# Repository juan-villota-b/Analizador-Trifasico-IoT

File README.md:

# Analizador Trifásico IoT

> Instrumento electrónico industrial de **medición eléctrica trifásica** con conectividad **IoT**.
> Orientado a instalaciones industriales y motores: registro de consumo, variables eléctricas a múltiples escalas de tiempo, comunicación **Modbus RTU / RS-485** y enlace inalámbrico **Wi-Fi HaLow**.

**Estado del diseño:** diseño final **Rev. 1.0 (05/11/2026)** — esquemáticos capturados, layout en curso.

---

## 🧭 Diagrama de bloques final

Este es el diseño vigente. Toda decisión de hardware debe ser consistente con este diagrama:

📎 [`Diagrama_de_bloques_final.pdf`](documentation/Diagrama_de_bloques_final.pdf) · [`PNG`](documentation/Diagrama_de_bloques_final.png) · [`SVG`](documentation/Diagrama_de_bloques_final.svg)

> El diagrama V2 (`documentation/Diagrama de bloquesv2.pdf`, 07/10/2026) se conserva como historial. El diseño vigente es el de esta página.

---

## 🔧 Arquitectura por bloque

### 1. Entrada de potencia trifásica

| Elemento | Componente | Notas |
|---|---|---|
| Entrada | **Red trifásica L1 / L2 / L3 / N** | **3P4W, 120/208 V** |
| Conector | **U301** — bornera 4 vías, 5 mm | N · L3 · L2 · L1, 10 A |
| Protección | **F300–F302** + **RV300–RV302** | Fusibles 2410 *time-lag* + MOV-14D471K por fase |
| Entrada de CT | **4× HX PJ-320A-3P DIP** (U300, U302, U303, U304) | Tres fases + neutro |

**Conexionado de los jacks de CT:** pin 2 = *tip* (señal), pin 3 = *sleeve* (retorno), pin 4 = *switch*. El pin 4 se une al pin 3 para cortocircuitar el CT cuando no hay plug; al insertar el plug, el switch abre y el CT queda con su burden. Cada pierna lleva **5.1 Ω** a AGND, **1 kΩ** en serie y **33 nF** de filtro.

> Hoja: `THREE PHASES.SchDoc`

### 2. Acondicionamiento analógico

| Elemento | Descripción |
|---|---|
| Canales de tensión | 3 canales diferenciales: **6×165 kΩ + 1 kΩ** por fase, **33 nF** a AGND |
| Canales de corriente | 4 canales diferenciales: burden **5.1 Ω** por pierna, **1 kΩ** serie, **33 nF** |
| Rango del AFE | **830 mVp** por canal diferencial |
| Filtrado | RC de entrada y guard ring en el layout |

El divisor de tensión usa resistencias de **165 kΩ ±0.1 %** y **1 kΩ** en la base. El burden de corriente es de **10.2 Ω diferencial** (5.1 Ω por pierna), compatible con un CT de **100 A / 40 mA** (577 mVp).

> Hoja: `THREE PHASES.SchDoc` (derivaciones) + `MEASURES.SchDoc`

### 3. AFE metrológico

| Elemento | Componente |
|---|---|
| Medidor | **RENERGY RN8302B** (LQFP-44) |
| Canales | 3 de tensión + 4 de corriente, diferenciales |
| Reloj | Cristal **8.192 MHz** (`049ss2-8.192f12dzlal`) |
| Desacople | 10 µF + 100 nF por riel, 1 µF local, ferrita FB100 |
| Alimentación | **AVCC/DVCC 3.3 V** desde el dominio de medida |

Calcula V, I, P, Q, S, PF y THD internamente. El ESP32-S3 lee los registros por SPI a través del ISO7741.

> Hoja: `MEASURES.SchDoc`

### 4. Aislamiento galvánico

| Elemento | Componente |
|---|---|
| Aislador digital | **TI ISO7741DWR** (4 canales, 5000 Vrms) |
| Alimentación aislada del AFE | **B0503S-1WR3** (5 V → 3.3 V, 1 W, 1500 VDC) |
| Señales aisladas | **SPI de 4 hilos** entre RN8302B y ESP32-S3 |

**Mapa del SPI aislado:**

| Señal | ESP32-S3 | ISO7741 | RN8302B |
|---|---|---|---|
| MOSI | `IO14` (pin 22) | INA 3 → OUTA 14 | SDI 35 |
| CS | `IO21` (pin 23) | INB 4 → OUTB 13 | SCSN 34 |
| CLK | `IO47` (pin 24) | INC 5 → OUTC 12 | SCLK 33 |
| MISO | `IO48` (pin 25) | OUTD 6 ← IND 11 | SDO 32 |

El dominio de medida queda referenciado a **AGND = N**; el dominio digital a **DGND**; el RS-485 a **RGND**. El ISO7741 y el B0503S son los puentes de la barrera.

> Hoja: `MEASURES.SchDoc`

### 5. Procesamiento

| Elemento | Componente |
|---|---|
| MCU | **ESP32-S3-WROOM-1-N4** |
| Programación | **USB-C** (`CON_USB_TYPEC_16P`) — USB nativo / JTAG integrado |
| Monitorización | Puerto serie por USB |
| Arranque | Botones **EN** y **BOOT**, RC de 10 kΩ + 1.1 µF |

> Hoja: `MCU.SchDoc`

### 6. Alimentación

| Riel | Componente | Capacidad | Destino |
|---|---|---|---|
| AC/DC principal | **Hi-Link HLK-10M05** | 5 V @ 2 A (10 W) | Riel de 5 V y respaldo |
| OR-ing de 5 V | **D200** (MS2A40LWS) | — | `Vin_buck_5V` |
| Carga de respaldo | **TPS2553DRVR** + **2×30 F** | 15 F equivalentes | *Last Gasp* |
| OR-ing de respaldo | **D201** (MS2A40LWS) | — | `Vin_buck_5V` |
| Riel digital | **AP63203WU-7** | **3.3 V @ 2 A** | ESP32-S3, SD, RS-485, HaLow |
| Riel de medida | **B0503S-1WR3** | **3.3 V @ 1 W aislado** | RN8302B, ISO7741 lado 2 |

#### Presupuesto de corriente del riel 3.3 V

| Carga | Consumo |
|---|---:|
| ESP32-S3-WROOM | 500 mA |
| Quectel FGH100M (Wi-Fi HaLow) | 350 mA |
| microSD | 200 mA |
| VISOM RSM3485PCT (RS-485) | 90 mA |
| RN8302B + ISO7741 | 20 mA |
| **Total** | **1 160 mA** |
| Capacidad del buck AP63203 | 2 000 mA |
| **Margen** | **840 mA (42 %)** |

#### Respaldo *Last Gasp*

- Banco: **2×30 F = 15 F** equivalentes, cargado a ≈4.6 V.
- Energía útil hasta ≈4.2 V: **≈26 J**.
- Autonomía: **≈8 s a 3.2 W**, suficiente para cerrar el registro y notificar.
- La rama de carga se limita con el **TPS2553**; el detalle de coordinación está en `REPORT.md`.

> Hoja: `POWER.SchDoc`

### 7. Periféricos

| Periférico | Componente | Interfaz con el ESP32-S3 | Consumo |
|---|---|---|---|
| **RS-485** | **VISOM RSM3485PCT** | UART `IO17/IO18` + `CON` `IO16` | 90 mA |
| **Wi-Fi HaLow** | **Quectel FGH100M** (módulo externo) | SPI compartido + control | 350 mA (3.3 V) |
| **Almacenamiento** | **microSD** (`tf-card-9p`) | SPI `IO11/IO12/IO13`, CS `IO38` | 200 mA |
| **USB** | **USB-C** | D−/D+ `IO19/IO20` | — |

**Conexión del módulo HaLow (headers 500/501):**

| Header | Pin | Señal | GPIO |
|---|---:|---|---|
| 500 | 1 | `RST_H` | `IO5` |
| 500 | 2 | `WK_IN_H` | `IO6` |
| 500 | 3 | `SPI_IRQ_H` | `IO7` |
| 500 | 4 | `SPI_CS_H` | `IO10` |
| 501 | 2 | `SPI_CLK_H` | `IO12` |
| 501 | 3 | `SPI_MISO_H` | `IO13` |
| 501 | 4 | `SPI_MOSI_H` | `IO11` |
| 501 | 5 | 3.3 V | — |
| 501 | 6 | DGND | — |
| 501 | 7 | 5 V | — |

La microSD y el FGH100M comparten el bus SPI (`IO11/IO12/IO13`) con CS independientes (`IO38` y `IO10`). El RN8302B tiene un bus SPI dedicado y aislado, por lo que no comparte MISO con la SD ni con el HaLow.

> Hojas: `MCU.SchDoc` + `INTERFACES.SchDoc`

---

## 📌 Mapa de interfaces del ESP32-S3-WROOM

| Interfaz | Pines | Hacia |
|---|---|---|
| SPI aislado del AFE | `IO14` MOSI, `IO21` CS, `IO47` CLK, `IO48` MISO | RN8302B vía ISO7741 |
| SPI de microSD / HaLow | `IO11` MOSI, `IO12` CLK, `IO13` MISO | microSD (`CS IO38`) y FGH100M (`CS IO10`) |
| UART RS-485 | `IO17` TX, `IO18` RX, `IO16` CON | RSM3485PCT |
| Control HaLow | `IO5` RST, `IO6` WAKE, `IO7` IRQ, `IO10` CS | Headers 500/501 |
| USB | `IO19` D−, `IO20` D+ | USB-C |
| Arranque | `IO0` BOOT, pin 3 EN | Botones y RC |
| Tarjeta SD | `IO9` CD | Conector microSD |

---

## ⚡ Arquitectura de energía

```
Red 3P4W 120/208 V
        │
        └──► U301 ─► F300 ─► HLK-10M05 (5 V @ 2 A)
                                   │
                                   └──► D200 ─► 5 V (Vin_buck_5V)
                                              ├──► AP63203 ─► 3.3 V digital
                                              │        └──► ESP32-S3 · microSD · RS-485 · HaLow
                                              ├──► TPS2553 ─► 2×30 F (15 F) ─► D201 ─► 5 V respaldo
                                              └──► B0503S-1WR3 ─► 3.3 V aislado ─► RN8302B + ISO7741
```

El **HLK-10M05** es la única fuente AC/DC y alimenta el riel de 5 V. El **AP63203** genera el riel digital de 3.3 V; el **B0503S-1WR3** genera el riel aislado de 3.3 V para el AFE. El **TPS2553** carga el banco de supercapacitores y el **D201** lo conecta al riel de 5 V durante el respaldo.

---

## 🗂️ Estructura del repositorio

```
Analizador trifasico IoT/
├── README.md
├── REPORT.md                       ← auditoría pin a pin y verificaciones de cierre
├── CONTRIBUTING.md                 ← guía de trabajo en equipo
├── INSTRUCCIONES.md                ← guía de layout y fabricación
├── AGENTS.md                       ← reglas para agentes de IA
├── .gitignore / .gitattributes
│
├── hardware/
│   ├── altium/                     ← Proyecto Altium Designer (fuente de verdad)
│   │   ├── Analizador_trifasico_IoT_pcb.PrjPcb
│   │   ├── Analizador_trifasico_IoT_pcb.PrjPcbStructure
│   │   ├── MAIN.SchDoc             ← hoja raíz
│   │   ├── THREE PHASES.SchDoc     ← entrada trifásica, CT y divisores
│   │   ├── POWER.SchDoc            ← alimentación, respaldo y rieles
│   │   ├── MEASURES.SchDoc         ← RN8302B + ISO7741 + cristal
│   │   ├── MCU.SchDoc              ← ESP32-S3, USB-C, EN/BOOT
│   │   ├── INTERFACES.SchDoc       ← RS-485, microSD, headers HaLow
│   │   └── Analizador_PCB.PcbDoc   ← layout
│   │
│   └── libraries/                  ← Biblioteca única del proyecto
│       ├── Library_Analizador.LibPkg
│       ├── Schlib1.SchLib
│       ├── PcbLib1.PcbLib
│       └── Library_Analizador.IntLib
│
├── documentation/
│   ├── Diagrama_de_bloques_final.pdf / .png / .svg
│   ├── Diagrama de bloquesv2.pdf   ← historial
│   ├── application-note/           ← nota de aplicación (LaTeX + PDF)
│   ├── revision_v3/                ← diagramas de la revisión anterior
│   ├── wifi-module-halow-xiao/     ← documentación del módulo HaLow
│   └── RD_EM_01_Industrial_Energy_Monitor.pdf
│
├── references/
│   ├── datasheets/
│   ├── application-notes/
│   └── reference-designs/
│
└── software/                       ← herramientas de visualización y pruebas
```

> `INSTRUCCIONES.md` conserva la guía de layout de la revisión anterior. Para la conectividad vigente usa `REPORT.md` y el netlist del 05/11/2026.

---

## 🔌 Hojas del esquemático

| # | Archivo | Contenido | Componentes clave |
|---|---|---|---|
| 1 | `MAIN.SchDoc` | Hoja raíz: solo *sheet symbols* | — |
| 2 | `THREE PHASES.SchDoc` | Entrada trifásica, CT y divisores | U301, F300–F302, RV300–RV302, U300/U302/U303/U304, R303–R339, C300–C313 |
| 3 | `POWER.SchDoc` | Alimentación, respaldo y rieles | HLK-10M05, D200/D201/D202, TPS2553, 2×30 F, AP63203, B0503S-1WR3 |
| 4 | `MEASURES.SchDoc` | AFE metrológico y aislamiento | RN8302B, ISO7741, cristal 8.192 MHz, desacople |
| 5 | `MCU.SchDoc` | Procesamiento y USB | ESP32-S3-WROOM-1-N4, USB-C, EN/BOOT |
| 6 | `INTERFACES.SchDoc` | Comunicaciones y almacenamiento | RSM3485PCT, tf-card-9p, headers 500/501, SM712 |

---

## 📚 Referencias técnicas

### `references/datasheets/`

| Archivo | Componente |
|---|---|
| `RN8302B_Datasheet_v3.pdf` | RENERGY RN8302B — AFE metrológico |
| `RN8302B_User_Manual_v1.1.pdf` | RENERGY RN8302B — manual de usuario |
| `ESP32-S3_Datasheet_en.pdf` | Espressif ESP32-S3 — SoC |
| `ESP32-S3_Technical_Reference_Manual_en.pdf` | Espressif ESP32-S3 — manual técnico |
| `ESP32-S3-WROOM_Module.pdf` | Espressif ESP32-S3-WROOM-1-N4 — módulo |
| `ISO7741DWR_Datasheet.pdf` | TI ISO7741 — aislador digital cuádruple |
| `EVISUN B0503S-1WR3.pdf` | B0503S-1WR3 — DC-DC aislado 5 V → 3.3 V |
| `TI TPS2553DRVR.pdf` | TPS2553 — interruptor/cargador limitado |
| `AP63203WU-7_Datasheet.pdf` | AP63203 — buck 3.3 V |
| `HLK-10M05_Datasheet.pdf` | Hi-Link HLK-10M05 — AC/DC 5 V 2 A |
| `RSM3485PCT_Datasheet.pdf` | VISOM RSM3485PCT — RS-485 aislado |
| `TF-CARD-9P_Datasheet.pdf` | Conector microSD |
| `HX-PJ-320A-3P_Datasheet.pdf` | Jack PJ-320A-3P |
| `Supercapacitor_Datasheet.pdf` | Supercapacitor HP-2R7-J306VYJ23 |
| `JFC2410-0200TS_Datasheet.pdf` | Fusible 2410 |
| `MOV-14D471K_Datasheet.pdf` | Varistor MOV-14D471K |

### `references/application-notes/`

| Archivo | Contenido |
|---|---|
| `TI_DUF27A_Application_Note.pdf` | TI DUF27A — nota de aplicación |
| `TI_DUF27A_Layout.pdf` | TI DUF27A — guías de layout |
| `wifi-halow-module-for-xiao.md` | Notas del módulo Wi-Fi HaLow |

### `references/reference-designs/`

| Carpeta | Contenido |
|---|---|
| `EVAL-ADE9430/` | Analog Devices EVAL-ADE9430 — referencia de AFE trifásico |
| `WI-FI_HALOW_FGH100M_EXT01_V30/` | Módulo HaLow: PCB, esquemático PDF e importación a Altium |
| `HX PJ-320A-3P DIP/` | Conector HX PJ-320A-3P DIP — footprint y símbolo |
| `TI_DCG_v3/` | Gerber / ODB++ de referencia |

---

## 🚀 Cómo empezar a colaborar

> 📘 **Guía completa paso a paso: [`CONTRIBUTING.md`](CONTRIBUTING.md)**

### Ciclo de trabajo

```bash
git checkout main
git pull
git checkout -b feature/mi-tarea
# ... trabajar en Altium, guardar y CERRAR Altium ...
git status
git add .
git commit -m "MEASURES: ajusta rango de ADC de corriente"
git push -u origin feature/mi-tarea
# → Pull Request en GitHub → revisión → merge → borrar rama
```

Si `main` avanzó antes del merge:

```bash
git checkout main && git pull
git checkout feature/mi-tarea
git merge main
git push
```

> ⚠️ **Cierra Altium antes de `git pull`, `git checkout` o `git merge`.** Si está abierto, sobrescribe el archivo al guardar y se pierde el trabajo del compañero.

### Reglas de colaboración

Los archivos `.SchDoc`, `.PcbDoc`, `.SchLib` y `.PcbLib` son **binarios** (contenedores OLE2):

| Git **SÍ** puede | Git **NO** puede |
|---|---|
| Guardar el historial completo | Mostrar diffs de contenido (`Binary files differ`) |
| Revertir a cualquier versión | Fusionar cambios automáticamente |
| Crear ramas independientes | Resolver conflictos de merge |

1. **Una persona por archivo a la vez.** En especial `Analizador_PCB.PcbDoc` — es monolítico.
2. **Una rama por tarea**, nunca trabajes directamente en `main`.
3. **Nunca dos personas en la misma rama ni el mismo archivo en dos ramas.**
4. **Cierra Altium antes de cualquier operación de Git.**
5. **Si hay conflicto de merge en un binario**, no lo edites a mano: coordina con el compañero y rehaz el cambio en Altium sobre la versión que quede en `main`.

---

## 📄 Convención de commits

```
<hoja o bloque>: <descripción corta en imperativo>

THREE PHASES: ajusta entrada de CT
POWER: actualiza respaldo de supercaps
MEASURES: ajusta desacople del RN8302B
MCU: conecta SPI de la microSD
INTERFACES: ordena headers del HaLow
PCB: enruta zona de potencia
LIB: actualiza símbolo del RSM3485PCT
DOC: actualiza diagrama de bloques final
```

---

## 📊 Estado del proyecto

**Diseño final**
- [x] Arquitectura de hardware Rev. 1.0 (05/11/2026)
- [x] Diagrama de bloques final (PDF/PNG/SVG)
- [x] Esquemáticos de las 6 hojas capturados
- [x] Netlist y BOM del proyecto
- [x] Biblioteca única del proyecto
- [x] Nota de aplicación y documentación de referencia

**Verificaciones de cierre antes de fabricar**

| Tema | Verificación |
|---|---|
| CT | Seleccionar el modelo (100 A / 40 mA recomendado), confirmar burden 5.1 Ω y 830 mVp. |
| Entrada | Confirmar 120/208 V, coordinación de F300 con el HLK-10M05 y U301/PE. |
| Aislamiento | Verificar creepage/clearance de AGND, DGND y RGND. |
| BOM | Reexportar desde el `.BomDoc` y verificar los 148 componentes. |
| Altium | ERC/DRC, huellas y `Library_Analizador.IntLib`. |
| HaLow | Confirmar pinout del FGH100M y cableado de los headers 500/501. |
| EMC / seguridad | Filtro EMI, ESD y definición del gabinete (Clase I/II). |
| Producción | Test points, fiduciales y revisión de Gerbers. |

> La auditoría detallada, los cálculos y las acciones de cierre están en [`REPORT.md`](REPORT.md).

---

## 📄 Licencia

Proyecto académico — Universidad Nacional de Colombia, Facultad de Ingeniería.
Uso académico. Verificar autorización institucional antes de cualquier distribución pública.

---

## 🔗 Enlaces útiles

- [Altium — Git Version Control](https://www.altium.com/documentation/altium-designer/using-external-version-control/git)
- [Altium — Using External Version Control](https://www.altium.com/documentation/altium-designer/using-external-version-control)
- [KiCad — importación de archivos Altium](https://dev-docs.kicad.org/en/import-formats/altium/index.html)

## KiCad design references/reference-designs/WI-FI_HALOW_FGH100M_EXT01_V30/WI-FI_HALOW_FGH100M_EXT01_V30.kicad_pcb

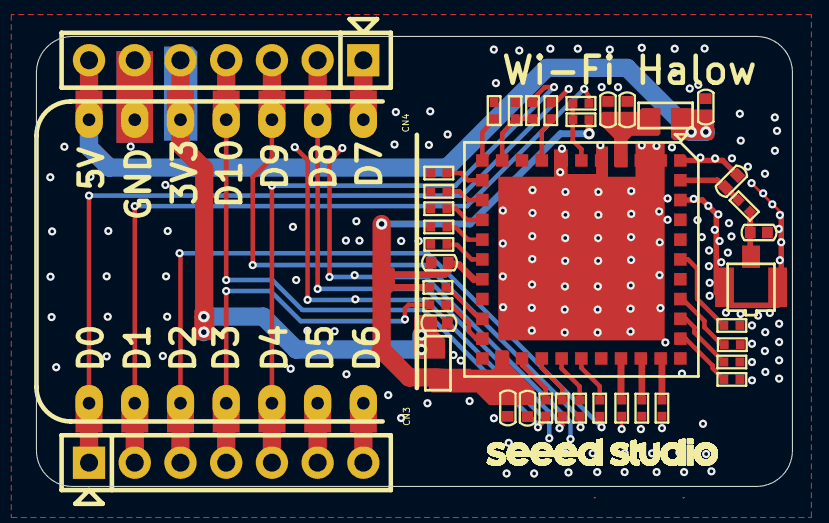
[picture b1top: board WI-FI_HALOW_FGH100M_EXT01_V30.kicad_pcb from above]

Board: 2 copper layers, 42.0 x 25.0 mm, 41 parts (0 on the bottom side), 40 nets.

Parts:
C1, C2, C3, C4, C5, C6, C7, C8, C9: C0402M
CN1: CON_U.FL-R-SMT-1
CN2: CN_ESP32S3_XIAO_DIP14
CN3, CN4: HEADER_PIN_SIP7_2MM54
FB1, FB2: FB0603
R1, R2, R3, R4, R5, R6, R7, R8, R9, R10, R11, R12, R13, R14, R15, R16, R17, R18, R19, R20, R21, R22, R23, R24, R25: R0402
UM1: FGH100M-H

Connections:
3V3: C4.1, CN2.12, CN4.5, FB1.1
ANT_WIFI: C1.1, CN1.1, R1.1
ANT_WIFI_MOD: C2.1, R1.2, UM1.40
BUSY: R15.2, R17.2, UM1.10
GND: C1.2, C2.2, C3.2, C4.2, C5.2, C6.2, C7.2, C8.2, C9.2, CN1.2, CN1.3, CN2.13, CN4.6, R2.2, R3.2, R4.2, R5.2, R6.2, R7.2, R8.2, R15.1, R18.1, R19.1, R20.1, R22.1, R23.1, R24.1, UM1.1, UM1.2, UM1.3, UM1.5, UM1.7, UM1.18, UM1.21, UM1.31, UM1.38, UM1.39, UM1.41, UM1.42, UM1.43, UM1.44, UM1.45, UM1.46, UM1.47, UM1.48, UM1.49, UM1.50, UM1.51, UM1.52, UM1.53, UM1.54, UM1.55, UM1.56, UM1.57, UM1.58, UM1.59, UM1.60, UM1.61, UM1.62, UM1.63, UM1.64, UM1.65
MOD_3V3: C7.1, C8.1, C9.1, FB1.2, R9.1, R25.2, UM1.17, UM1.22
MOD_5V: C5.1, C6.1, FB2.2, UM1.4
N34310028: R6.1, UM1.30
N34310043: R7.1, UM1.29
N34310055: R8.1, UM1.28
N34310477: R18.2, UM1.11
N34310504: R19.2, UM1.12
N34310586: R20.2, UM1.13
N34310613: R22.2, UM1.14
N34310640: R23.2, UM1.15
N34310667: R24.2, UM1.16
N34311591: R25.1, UM1.19
N34312565: R5.1, UM1.32
N34312570: R4.1, UM1.33
N34312575: R3.1, UM1.34
N34312580: R2.1, UM1.36
PA02_A0_D0: CN2.1, CN3.1, R13.1
PA4_A1_D1: CN2.2, CN3.2, R10.1
PA5_A9_D9_MISO: CN2.10, CN4.3, R12.2
PA6_A10_D10_MOSI: CN2.11, CN4.4, R16.2
PA7_A8_D8_SCK: CN2.9, CN4.2, R14.2
PA8_A4_D4_SDA: CN2.5, CN3.5, R17.1
PA9_A5_D5_SCL: CN2.6, CN3.6
PA10_A2_D2: CN2.3, CN3.3, R11.2
PA11_A3_D3: CN2.4, CN3.4, R21.2
PB08_A6_D6_TX: CN2.7, CN3.7
PB09_A7_D7_RX: CN2.8, CN4.1
RESET: R13.2, UM1.8
SPI_CLK: R14.1, UM1.24
SPI_CS: R21.1, UM1.20
SPI_INT: R11.1, UM1.26
SPI_MISO: R12.1, UM1.25
SPI_MOSI: R16.1, UM1.23
VDD_5V: C3.1, CN2.14, CN4.7, FB2.1
WAKEUP_IN: R9.2, R10.2, UM1.6
